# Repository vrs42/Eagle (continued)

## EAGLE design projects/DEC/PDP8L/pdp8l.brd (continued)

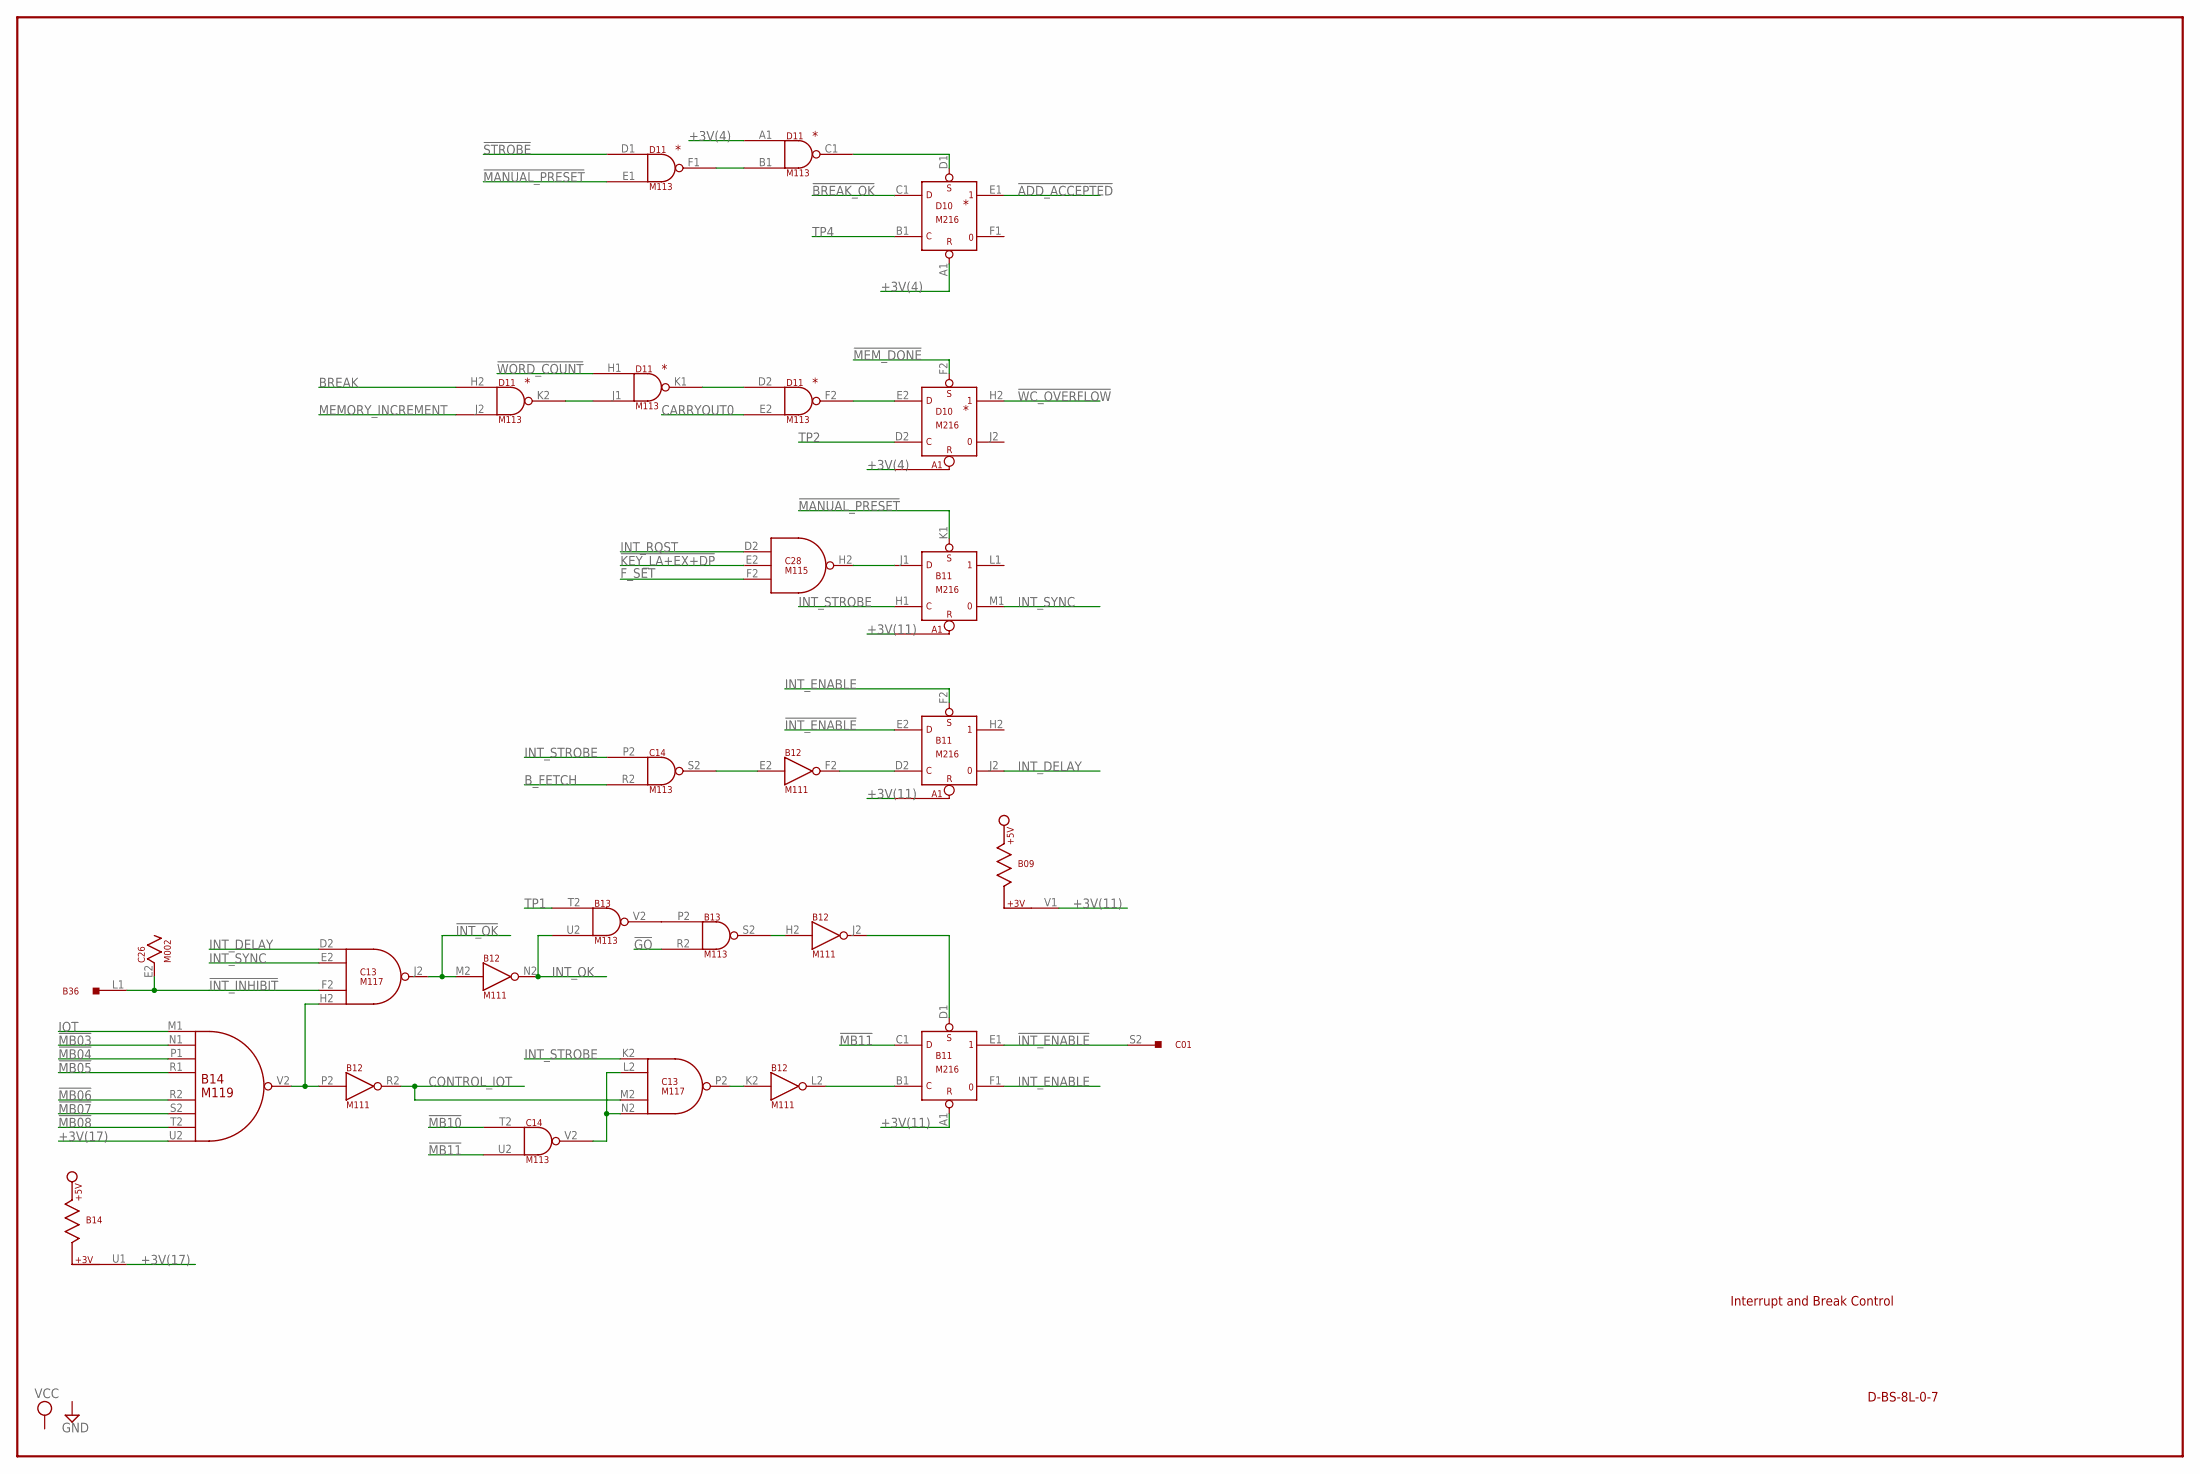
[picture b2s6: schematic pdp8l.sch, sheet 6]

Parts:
B09: M617; H807
B11: M216; H807
B12: M111; H807
B13: M113; H807
B14: M119; H807
B36: M903; H807
C01: G921; H807
C13: M117; H807
C14: M113; H807
C26: M002; H807
C28: M115; H807
D10: M216; H807
D11: M113; H807

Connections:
!ADD_ACCEPTED: D10.E1 (1); also elsewhere on the board
!BREAK_OK: D10.C1 (D); also elsewhere on the board
!GO: B13.R2 (IN2); also elsewhere on the board
!INT_ENABLE: B11.E1 (1), B11.E2 (D), C01.S2
!INT_INHIBIT: B36.L1, C13.F2 (IN3), C26.E2
!INT_OK: B12.M2 (IN), C13.J2 (OUT); also elsewhere on the board
!KEY_LA+EX+DP: C28.E2 (IN2); also elsewhere on the board
!MANUAL_PRESET: B11.K1 (S), D11.E1 (IN2); also elsewhere on the board
!MB03: B14.N1 (IN2); also elsewhere on the board
!MB04: B14.P1 (IN3); also elsewhere on the board
!MB05: B14.R1 (IN4); also elsewhere on the board
!MB06: B14.R2 (IN5); also elsewhere on the board
!MB07: B14.S2 (IN6); also elsewhere on the board
!MB08: B14.T2 (IN7); also elsewhere on the board
!MB10: C14.T2 (IN1); also elsewhere on the board
!MB11: B11.C1 (D), C14.U2 (IN2); also elsewhere on the board
!MEM_DONE: D10.F2 (S); also elsewhere on the board
!STROBE: D11.D1 (IN1); also elsewhere on the board
!WC_OVERFLOW: D10.H2 (1); also elsewhere on the board
!WORD_COUNT: D11.H1 (IN1); also elsewhere on the board
+3V(4): D10.A1 (R), D11.A1 (IN1); also elsewhere on the board
+3V(11): B09.V1, B11.A1 (R); also elsewhere on the board
+3V(17): B14.U1, B14.U2 (IN8)
B12F2: B11.D2 (C), B12.F2 (OUT)
B12J2: B11.D1 (S), B12.J2 (OUT)
B12L2: B11.B1 (C), B12.L2 (OUT)
B13S2: B12.H2 (IN), B13.S2 (OUT)
B13V2: B13.P2 (IN1), B13.V2 (OUT)
B14V2: B12.P2 (IN), B14.V2 (OUT), C13.H2 (IN4)
BREAK: D11.H2 (IN1); also elsewhere on the board
B_FETCH: C14.R2 (IN2); also elsewhere on the board
C13P2: B12.K2 (IN), C13.P2 (OUT)
C14S2: B12.E2 (IN), C14.S2 (OUT)
C14V2: C13.L2 (IN2), C13.N2 (IN4), C14.V2 (OUT)
C28H2: B11.J1 (D), C28.H2 (OUT)
CARRYOUT0: D11.E2 (IN2); also elsewhere on the board
CONTROL_IOT: B12.R2 (OUT), C13.M2 (IN3)
D11C1: D10.D1 (S), D11.C1 (OUT)
D11F1: D11.B1 (IN2), D11.F1 (OUT)
D11F2: D10.E2 (D), D11.F2 (OUT)
D11K1: D11.D2 (IN1), D11.K1 (OUT)
D11K2: D11.J1 (IN2), D11.K2 (OUT)
F_SET: C28.F2 (IN3); also elsewhere on the board
GND: B09.C2 (GND), B09.T1 (GND), B11.C2 (GND), B11.T1 (GND), B12.C2 (GND), B12.T1 (GND), B13.C2 (GND), B13.T1 (GND), B14.C2 (GND), B14.T1 (GND), B36.A1 (GND), B36.C1 (GND), B36.C2 (GND), B36.F1 (GND), B36.F2 (GND), B36.J2 (GND), B36.K1 (GND), B36.L2 (GND), B36.N1 (GND), B36.N2 (GND), B36.R1 (GND), B36.R2 (GND), B36.T1 (GND), B36.U2 (GND), C13.C2 (GND), C13.T1 (GND), C14.C2 (GND), C14.T1 (GND), C26.C2 (GND), C28.C2 (GND), C28.T1 (GND), D10.C2 (GND), D10.T1 (GND), D11.C2 (GND), D11.T1 (GND); also elsewhere on the board
INT_DELAY: B11.J2 (0), C13.D2 (IN1)
INT_ENABLE: B11.F1 (0), B11.F2 (S)
INT_OK: B12.N2 (OUT), B13.U2 (IN2); also elsewhere on the board
INT_RQST: C28.D2 (IN1); also elsewhere on the board
INT_STROBE: B11.H1 (C), C13.K2 (IN1), C14.P2 (IN1); also elsewhere on the board
INT_SYNC: B11.M1 (0), C13.E2 (IN2)
IOT: B14.M1 (IN1); also elsewhere on the board
MEMORY_INCREMENT: D11.J2 (IN2); also elsewhere on the board
TP1: B13.T2 (IN1); also elsewhere on the board
TP2: D10.D2 (C); also elsewhere on the board
TP4: D10.B1 (C); also elsewhere on the board
VCC: B09.A2 (VCC), B11.A2 (VCC), B12.A2 (VCC), B13.A2 (VCC), B14.A2 (VCC), C13.A2 (VCC), C14.A2 (VCC), C26.A2 (VCC), C28.A2 (VCC), D10.A2 (VCC), D11.A2 (VCC); also elsewhere on the board

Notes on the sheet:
D-BS-8L-0-7
Interrupt and Break Control

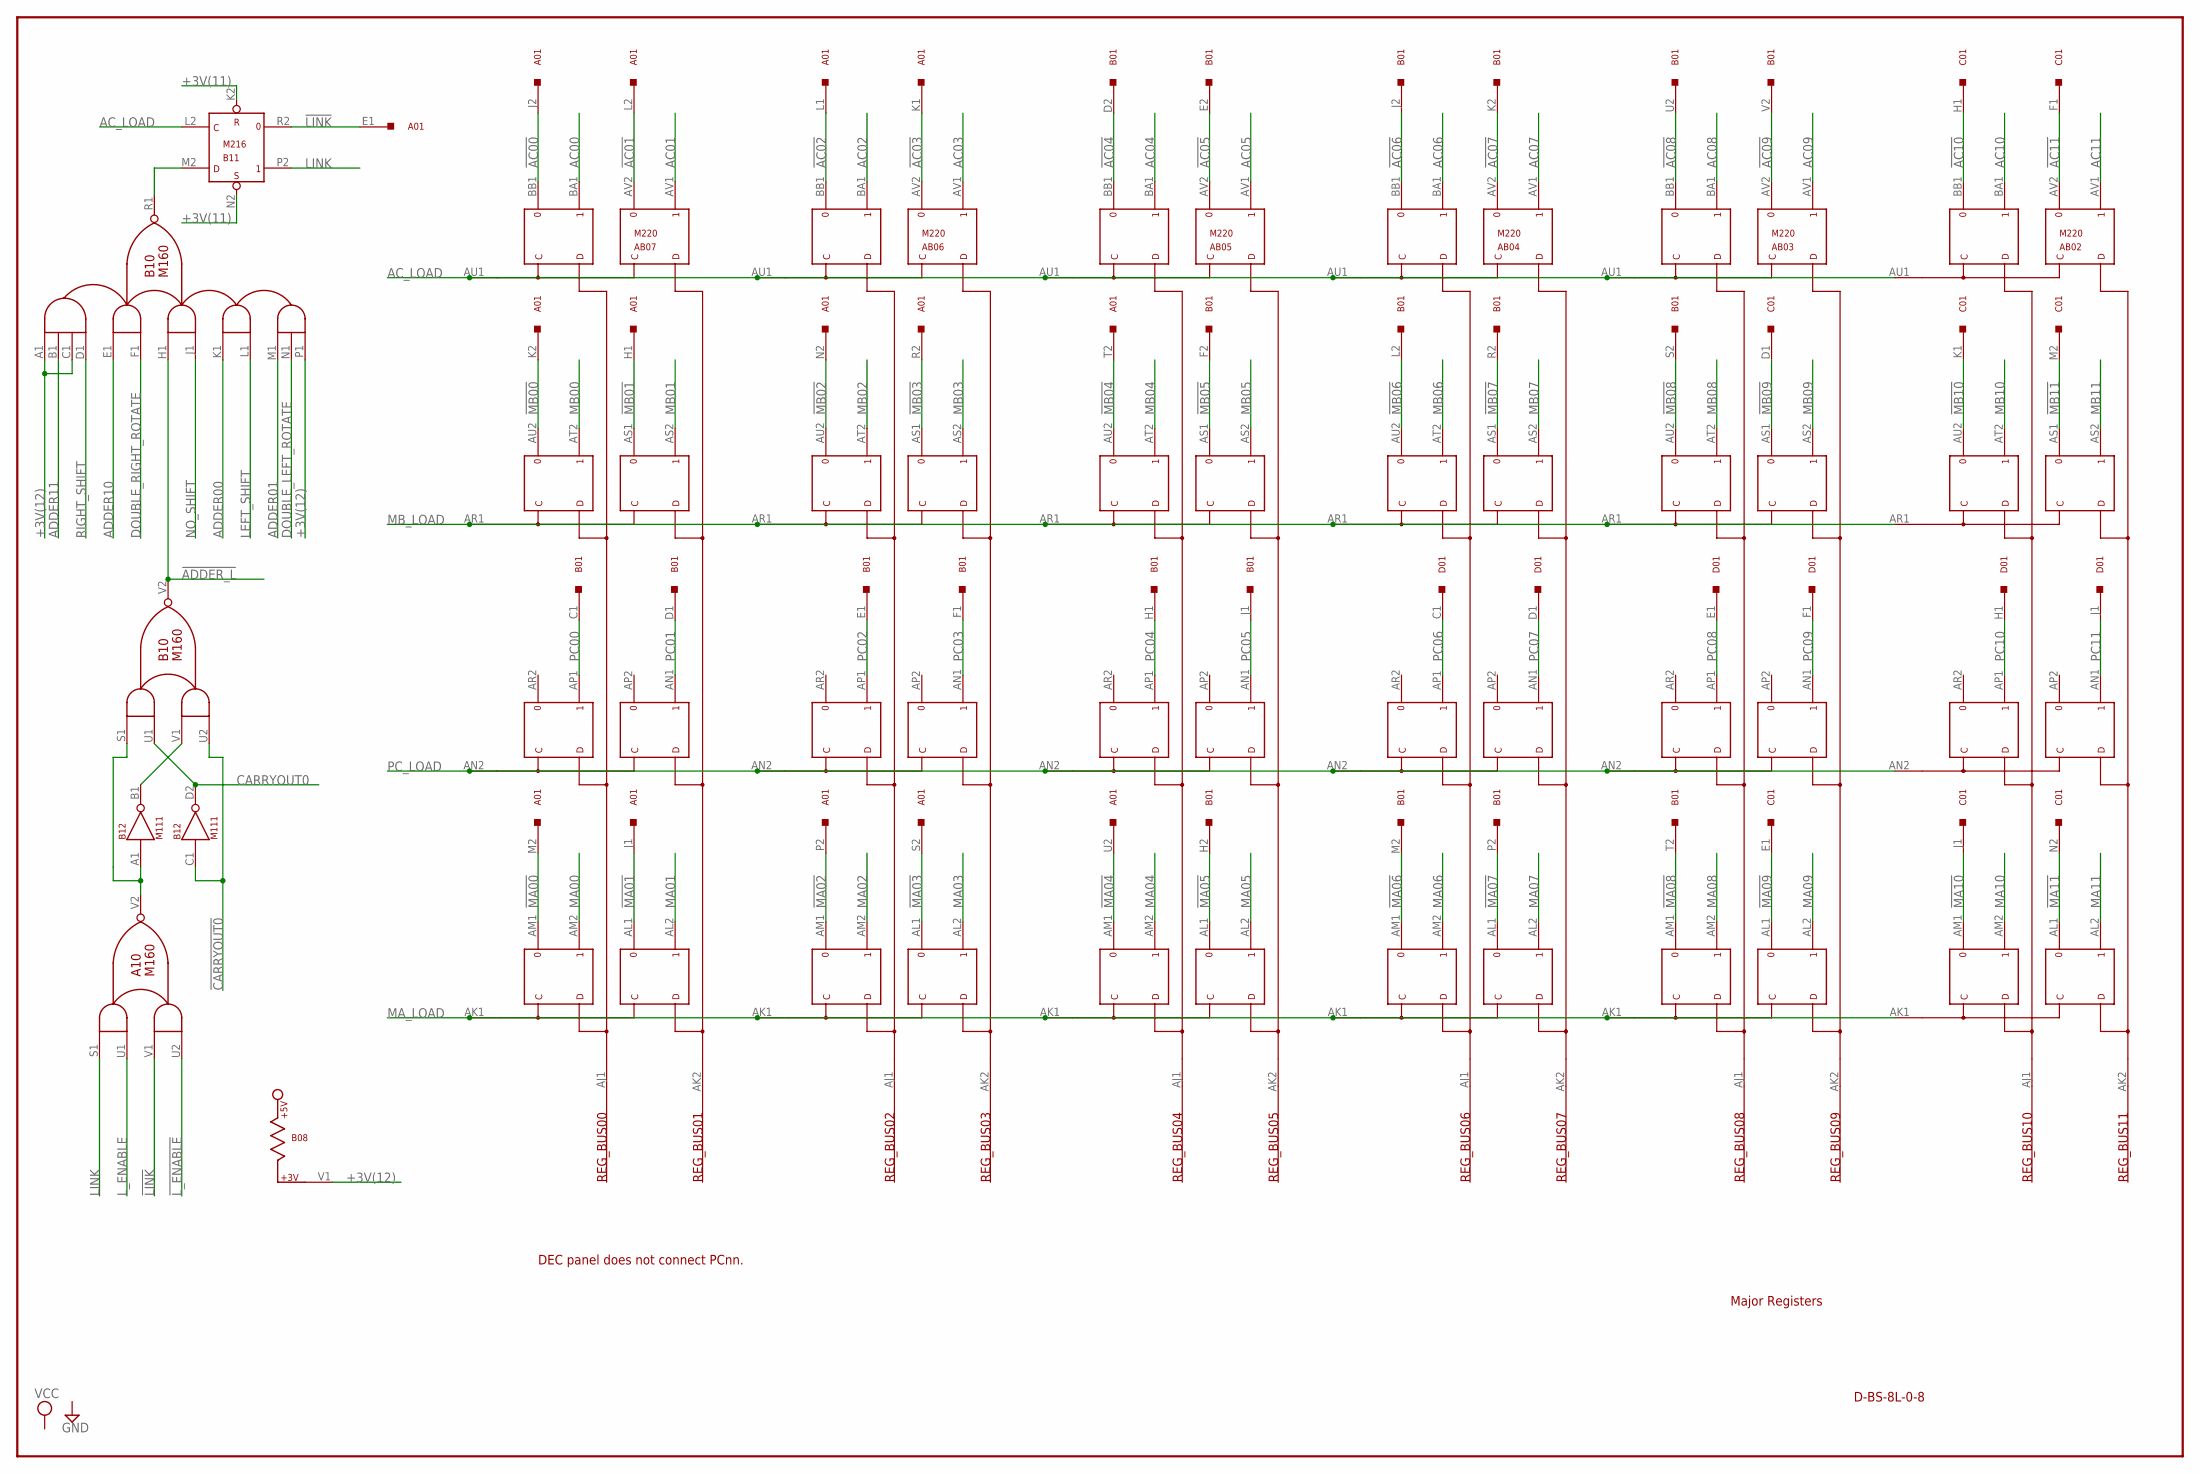
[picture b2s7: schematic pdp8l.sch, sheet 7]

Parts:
A01: G921; H807
A10: M160; H807
AB02, AB03, AB04, AB05, AB06, AB07: M220; H807-2
B01: G921; H807
B08: M617; H807
B10: M160; H807
B11: M216; H807
B12: M111; H807
C01: G921; H807
D01: G921; H807

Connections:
!AC00: A01.J2, AB07.BB1; also elsewhere on the board
!AC01: A01.L2, AB07.AV2; also elsewhere on the board
!AC02: A01.L1, AB06.BB1; also elsewhere on the board
!AC03: A01.K1, AB06.AV2; also elsewhere on the board
!AC04: AB05.BB1, B01.D2; also elsewhere on the board
!AC05: AB05.AV2, B01.E2; also elsewhere on the board
!AC06: AB04.BB1, B01.J2; also elsewhere on the board
!AC07: AB04.AV2, B01.K2; also elsewhere on the board
!AC08: AB03.BB1, B01.U2; also elsewhere on the board
!AC09: AB03.AV2, B01.V2; also elsewhere on the board
!AC10: AB02.BB1, C01.H1; also elsewhere on the board
!AC11: AB02.AV2, C01.F1; also elsewhere on the board
!ADDER_L: B10.H1 (IN3A), B10.V2 (OUT); also elsewhere on the board
!CARRYOUT0: B10.U2 (IN2B), B12.C1 (IN); also elsewhere on the board
!LINK: A01.E1, A10.V1 (IN2A), B11.R2 (0)
!L_ENABLE: A10.U2 (IN2B); also elsewhere on the board
!MA00: A01.M2, AB07.AM1; also elsewhere on the board
!MA01: A01.J1, AB07.AL1; also elsewhere on the board
!MA02: A01.P2, AB06.AM1; also elsewhere on the board
!MA03: A01.S2, AB06.AL1; also elsewhere on the board
!MA04: A01.U2, AB05.AM1; also elsewhere on the board
!MA05: AB05.AL1, B01.H2; also elsewhere on the board
!MA06: AB04.AM1, B01.M2; also elsewhere on the board
!MA07: AB04.AL1, B01.P2; also elsewhere on the board
!MA08: AB03.AM1, B01.T2; also elsewhere on the board
!MA09: AB03.AL1, C01.E1; also elsewhere on the board
!MA10: AB02.AM1, C01.J1; also elsewhere on the board
!MA11: AB02.AL1, C01.N2; also elsewhere on the board
!MB00: A01.K2, AB07.AU2; also elsewhere on the board
!MB01: A01.H1, AB07.AS1; also elsewhere on the board
!MB02: A01.N2, AB06.AU2; also elsewhere on the board
!MB03: A01.R2, AB06.AS1; also elsewhere on the board
!MB04: A01.T2, AB05.AU2; also elsewhere on the board
!MB05: AB05.AS1, B01.F2; also elsewhere on the board
!MB06: AB04.AU2, B01.L2; also elsewhere on the board
!MB07: AB04.AS1, B01.R2; also elsewhere on the board
!MB08: AB03.AU2, B01.S2; also elsewhere on the board
!MB09: AB03.AS1, C01.D1; also elsewhere on the board
!MB10: AB02.AU2, C01.K1; also elsewhere on the board
!MB11: AB02.AS1, C01.M2; also elsewhere on the board
+3V(11): B11.K2 (R), B11.N2 (S); also elsewhere on the board
+3V(12): B08.V1, B10.A1 (IN1A), B10.C1 (IN1C), B10.P1 (IN5C)
A10V2: A10.V2 (OUT), B10.S1 (IN1A), B12.A1 (IN)
AC00: AB07.BA1; also elsewhere on the board
AC01: AB07.AV1; also elsewhere on the board
AC02: AB06.BA1; also elsewhere on the board
AC03: AB06.AV1; also elsewhere on the board
AC04: AB05.BA1; also elsewhere on the board
AC05: AB05.AV1; also elsewhere on the board
AC06: AB04.BA1; also elsewhere on the board
AC07: AB04.AV1; also elsewhere on the board
AC08: AB03.BA1; also elsewhere on the board
AC09: AB03.AV1; also elsewhere on the board
AC10: AB02.BA1; also elsewhere on the board
AC11: AB02.AV1; also elsewhere on the board
AC_LOAD: AB02.AU1, AB03.AU1, AB04.AU1, AB05.AU1, AB06.AU1, AB07.AU1, B11.L2 (C); also elsewhere on the board
ADDER00: B10.K1 (IN4A); also elsewhere on the board
ADDER01: B10.M1 (IN5A); also elsewhere on the board
ADDER10: B10.E1 (IN2A); also elsewhere on the board
ADDER11: B10.B1 (IN1B); also elsewhere on the board
B10R1: B10.R1 (OUT), B11.M2 (D)
B12B1: B10.V1 (IN2A), B12.B1 (OUT)
CARRYOUT0: B10.U1 (IN1B), B12.D2 (OUT); also elsewhere on the board
DOUBLE_LEFT_ROTATE: B10.N1 (IN5B); also elsewhere on the board
DOUBLE_RIGHT_ROTATE: B10.F1 (IN2B); also elsewhere on the board
GND: A10.C2 (GND), A10.T1 (GND), AB02.AC2 (GND), AB02.AT1 (GND), AB02.BC2 (GND), AB02.BT1 (GND), AB03.AC2 (GND), AB03.AT1 (GND), AB03.BC2 (GND), AB03.BT1 (GND), AB04.AC2 (GND), AB04.AT1 (GND), AB04.BC2 (GND), AB04.BT1 (GND), AB05.AC2 (GND), AB05.AT1 (GND), AB05.BC2 (GND), AB05.BT1 (GND), AB06.AC2 (GND), AB06.AT1 (GND), AB06.BC2 (GND), AB06.BT1 (GND), AB07.AC2 (GND), AB07.AT1 (GND), AB07.BC2 (GND), AB07.BT1 (GND), B08.C2 (GND), B08.T1 (GND), B10.C2 (GND), B10.T1 (GND), B11.C2 (GND), B11.T1 (GND), B12.C2 (GND), B12.T1 (GND); also elsewhere on the board
LEFT_SHIFT: B10.L1 (IN4B); also elsewhere on the board
LINK: A10.S1 (IN1A), B11.P2 (1); also elsewhere on the board
L_ENABLE: A10.U1 (IN1B); also elsewhere on the board
MA00: AB07.AM2; also elsewhere on the board
MA01: AB07.AL2; also elsewhere on the board
MA02: AB06.AM2; also elsewhere on the board
MA03: AB06.AL2; also elsewhere on the board
MA04: AB05.AM2; also elsewhere on the board
MA05: AB05.AL2; also elsewhere on the board
MA06: AB04.AM2; also elsewhere on the board
MA07: AB04.AL2; also elsewhere on the board
MA08: AB03.AM2; also elsewhere on the board
MA09: AB03.AL2; also elsewhere on the board
MA10: AB02.AM2; also elsewhere on the board
MA11: AB02.AL2; also elsewhere on the board
MA_LOAD: AB02.AK1, AB03.AK1, AB04.AK1, AB05.AK1, AB06.AK1, AB07.AK1; also elsewhere on the board
MB00: AB07.AT2; also elsewhere on the board
MB01: AB07.AS2; also elsewhere on the board
MB02: AB06.AT2; also elsewhere on the board
MB03: AB06.AS2; also elsewhere on the board
MB04: AB05.AT2; also elsewhere on the board
MB05: AB05.AS2; also elsewhere on the board
MB06: AB04.AT2; also elsewhere on the board
MB07: AB04.AS2; also elsewhere on the board
MB08: AB03.AT2; also elsewhere on the board
MB09: AB03.AS2; also elsewhere on the board
MB10: AB02.AT2; also elsewhere on the board
MB11: AB02.AS2; also elsewhere on the board
MB_LOAD: AB02.AR1, AB03.AR1, AB04.AR1, AB05.AR1, AB06.AR1, AB07.AR1; also elsewhere on the board
NO_SHIFT: B10.J1 (IN3B); also elsewhere on the board
PC00: AB07.AP1, B01.C1
PC01: AB07.AN1, B01.D1
PC02: AB06.AP1, B01.E1
PC03: AB06.AN1, B01.F1
PC04: AB05.AP1, B01.H1
PC05: AB05.AN1, B01.J1
PC06: AB04.AP1, D01.C1
PC07: AB04.AN1, D01.D1
PC08: AB03.AP1, D01.E1
PC09: AB03.AN1, D01.F1
PC10: AB02.AP1, D01.H1
PC11: AB02.AN1, D01.J1
PC_LOAD: AB02.AN2, AB03.AN2, AB04.AN2, AB05.AN2, AB06.AN2, AB07.AN2; also elsewhere on the board
RIGHT_SHIFT: B10.D1 (IN1D); also elsewhere on the board
VCC: A10.A2 (VCC), AB02.AA2 (VCC), AB02.BA2 (VCC), AB03.AA2 (VCC), AB03.BA2 (VCC), AB04.AA2 (VCC), AB04.BA2 (VCC), AB05.AA2 (VCC), AB05.BA2 (VCC), AB06.AA2 (VCC), AB06.BA2 (VCC), AB07.AA2 (VCC), AB07.BA2 (VCC), B08.A2 (VCC), B10.A2 (VCC), B11.A2 (VCC), B12.A2 (VCC); also elsewhere on the board

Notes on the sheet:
Major Registers
D-BS-8L-0-8
REG_BUS00
REG_BUS01
REG_BUS02
REG_BUS03
REG_BUS04
REG_BUS05
REG_BUS06
REG_BUS07
REG_BUS08
REG_BUS09
REG_BUS10
REG_BUS11
DEC panel does not connect PCnn.

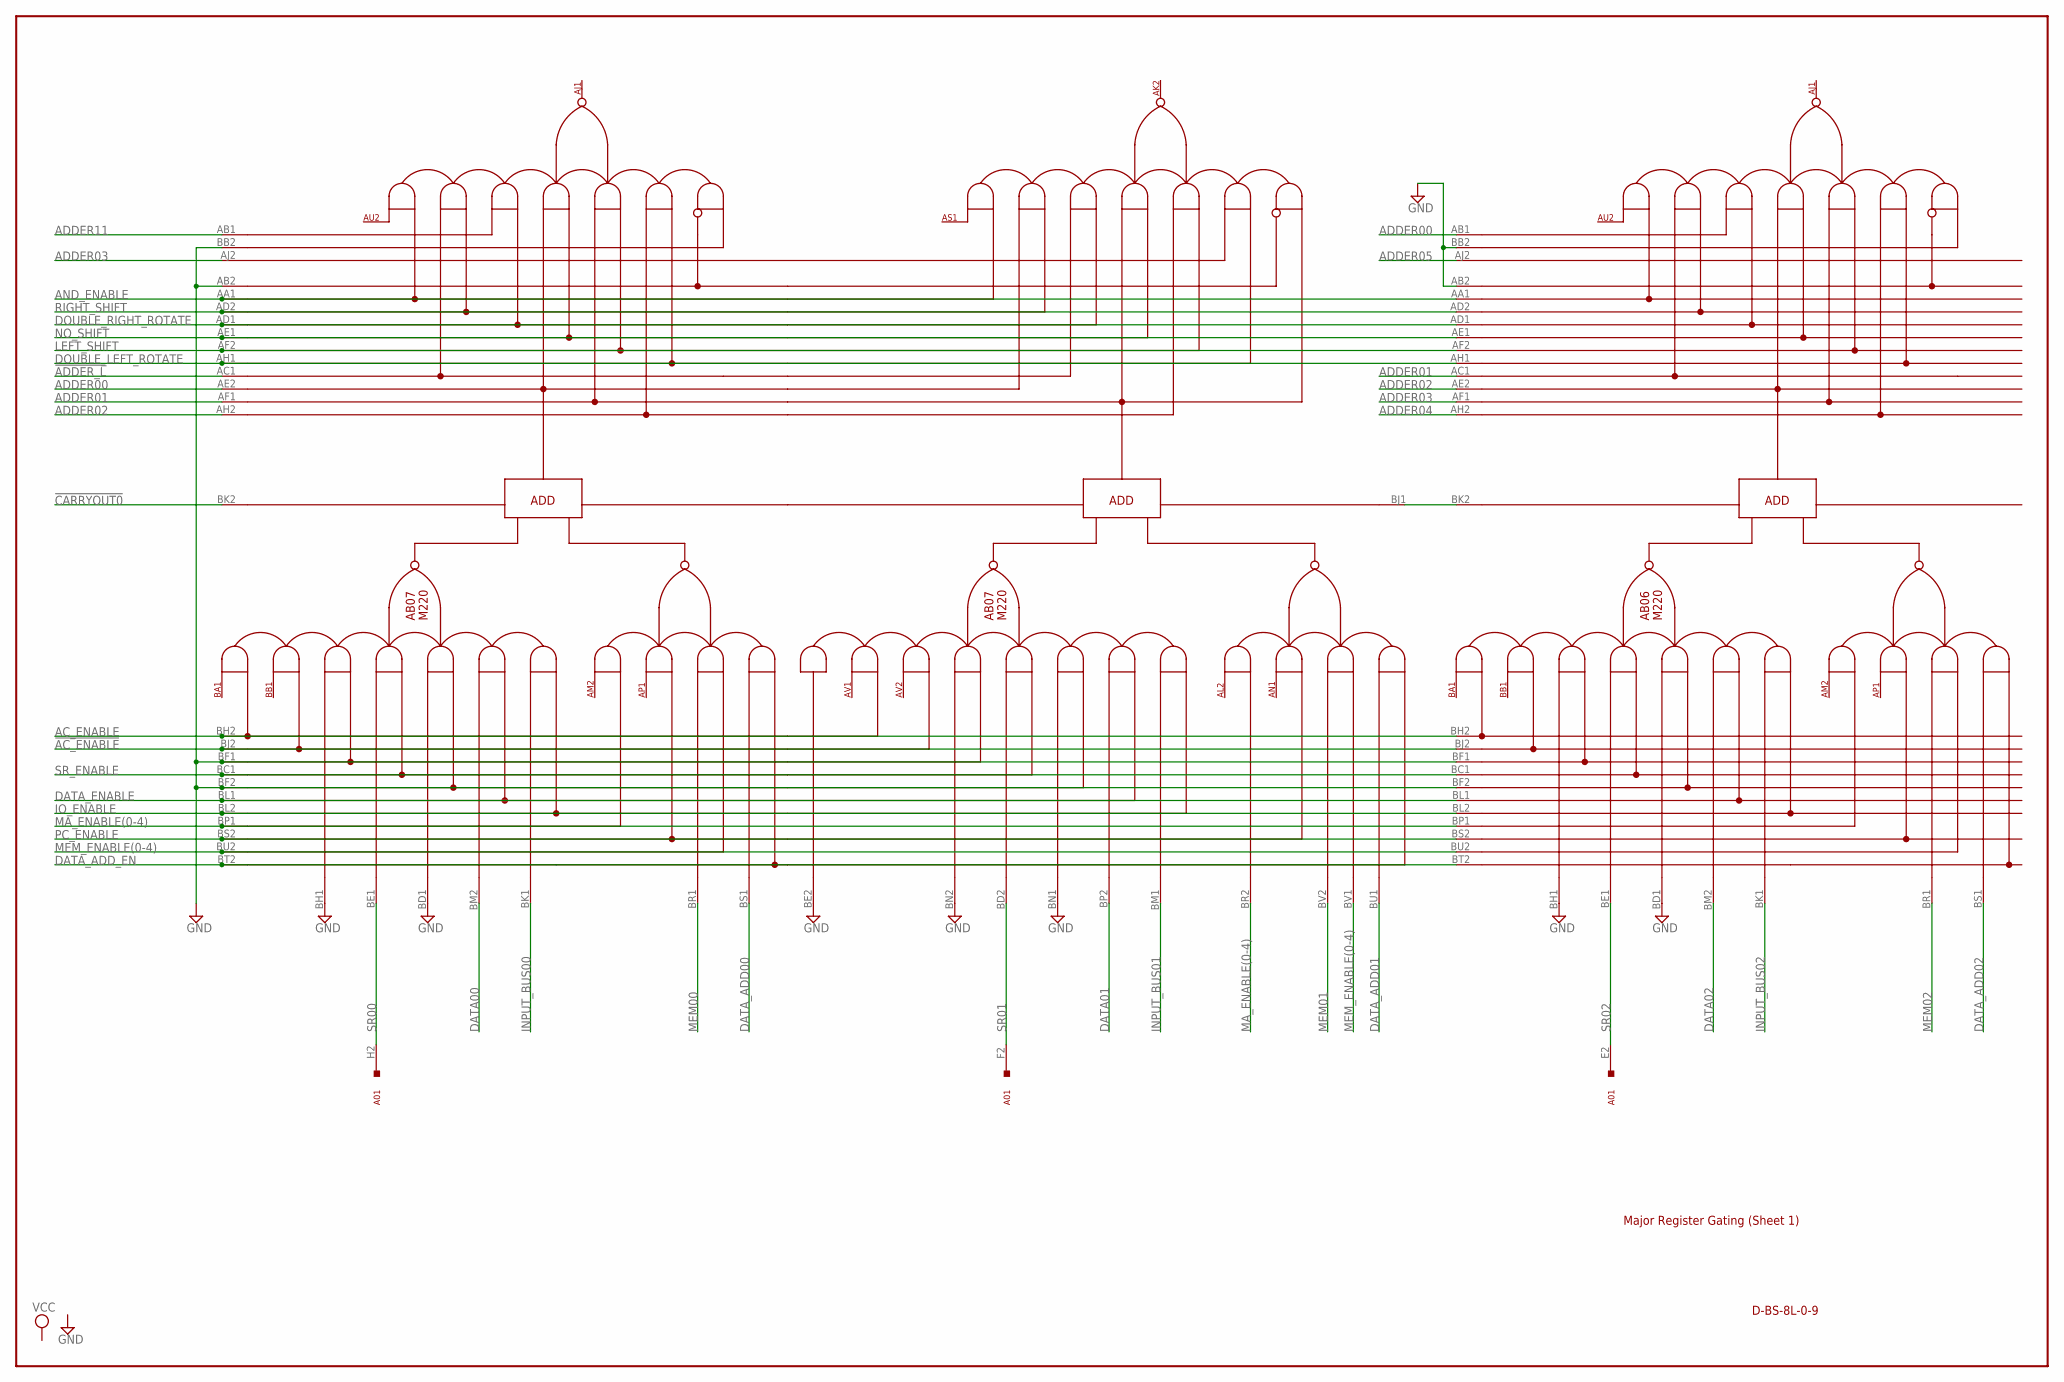
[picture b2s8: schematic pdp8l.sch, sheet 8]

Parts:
A01: G921; H807
AB06, AB07: M220; H807-2

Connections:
!AC_ENABLE: AB06.BJ2, AB07.BJ2; also elsewhere on the board
!ADDER_L: AB07.AC1; also elsewhere on the board
!CARRYOUT0: AB07.BK2; also elsewhere on the board
!CARRYOUT2: AB06.BK2, AB07.BJ1
AC_ENABLE: AB06.BH2, AB07.BH2; also elsewhere on the board
ADDER00: AB06.AB1, AB07.AE2; also elsewhere on the board
ADDER01: AB06.AC1, AB07.AF1; also elsewhere on the board
ADDER02: AB06.AE2, AB07.AH2; also elsewhere on the board
ADDER03: AB06.AF1, AB07.AJ2; also elsewhere on the board
ADDER04: AB06.AH2; also elsewhere on the board
ADDER05: AB06.AJ2; also elsewhere on the board
ADDER11: AB07.AB1; also elsewhere on the board
AND_ENABLE: AB06.AA1, AB07.AA1; also elsewhere on the board
DATA00: AB07.BM2; also elsewhere on the board
DATA01: AB07.BP2; also elsewhere on the board
DATA02: AB06.BM2; also elsewhere on the board
DATA_ADD00: AB07.BS1; also elsewhere on the board
DATA_ADD01: AB07.BU1; also elsewhere on the board
DATA_ADD02: AB06.BS1; also elsewhere on the board
DATA_ADD_EN: AB06.BT2, AB07.BT2; also elsewhere on the board
DATA_ENABLE: AB06.BL1, AB07.BL1; also elsewhere on the board
DOUBLE_LEFT_ROTATE: AB06.AH1, AB07.AH1; also elsewhere on the board
DOUBLE_RIGHT_ROTATE: AB06.AD1, AB07.AD1; also elsewhere on the board
GND: AB06.AB2, AB06.AC2 (GND), AB06.AT1 (GND), AB06.BB2, AB06.BC2 (GND), AB06.BD1, AB06.BF1, AB06.BF2, AB06.BH1, AB06.BT1 (GND), AB07.AB2, AB07.AC2 (GND), AB07.AT1 (GND), AB07.BB2, AB07.BC2 (GND), AB07.BD1, AB07.BE2, AB07.BF1, AB07.BF2, AB07.BH1, AB07.BN1, AB07.BN2, AB07.BT1 (GND); also elsewhere on the board
INPUT_BUS00: AB07.BK1; also elsewhere on the board
INPUT_BUS01: AB07.BM1; also elsewhere on the board
INPUT_BUS02: AB06.BK1; also elsewhere on the board
IO_ENABLE: AB06.BL2, AB07.BL2; also elsewhere on the board
LEFT_SHIFT: AB06.AF2, AB07.AF2; also elsewhere on the board
MA_ENABLE(0-4): AB06.BP1, AB07.BP1, AB07.BR2; also elsewhere on the board
MEM00: AB07.BR1; also elsewhere on the board
MEM01: AB07.BV2; also elsewhere on the board
MEM02: AB06.BR1; also elsewhere on the board
MEM_ENABLE(0-4): AB06.BU2, AB07.BU2, AB07.BV1; also elsewhere on the board
NO_SHIFT: AB06.AE1, AB07.AE1; also elsewhere on the board
PC_ENABLE: AB06.BS2, AB07.BS2; also elsewhere on the board
RIGHT_SHIFT: AB06.AD2, AB07.AD2; also elsewhere on the board
SR00: A01.H2, AB07.BE1
SR01: A01.F2, AB07.BD2
SR02: A01.E2, AB06.BE1
SR_ENABLE: AB06.BC1, AB07.BC1; also elsewhere on the board
VCC: AB06.AA2 (VCC), AB06.BA2 (VCC), AB07.AA2 (VCC), AB07.BA2 (VCC); also elsewhere on the board

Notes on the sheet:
Major Register Gating (Sheet 1)
D-BS-8L-0-9

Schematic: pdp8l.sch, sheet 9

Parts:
A01: G921; H807
AB05, AB06: M220; H807-2
C01: G921; H807

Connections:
!AC_ENABLE: AB05.BJ2; also elsewhere on the board
!CARRYOUT4: AB05.BK2, AB06.BJ1
!CARRYOUT6: AB05.BJ1; also elsewhere on the board
AC_ENABLE: AB05.BH2; also elsewhere on the board
ADDER02: AB05.AB1; also elsewhere on the board
ADDER03: AB05.AC1; also elsewhere on the board
ADDER04: AB05.AE2; also elsewhere on the board
ADDER05: AB05.AF1; also elsewhere on the board
ADDER06: AB05.AH2; also elsewhere on the board
ADDER07: AB05.AJ2; also elsewhere on the board
AND_ENABLE: AB05.AA1; also elsewhere on the board
DATA03: AB06.BP2; also elsewhere on the board
DATA04: AB05.BM2; also elsewhere on the board
DATA05: AB05.BP2; also elsewhere on the board
DATA_ADD03: AB06.BU1; also elsewhere on the board
DATA_ADD04: AB05.BS1; also elsewhere on the board
DATA_ADD05: AB05.BU1; also elsewhere on the board
DATA_ADD_EN: AB05.BT2; also elsewhere on the board
DATA_ENABLE: AB05.BL1; also elsewhere on the board
DOUBLE_LEFT_ROTATE: AB05.AH1; also elsewhere on the board
DOUBLE_RIGHT_ROTATE: AB05.AD1; also elsewhere on the board
GND: AB05.AB2, AB05.AC2 (GND), AB05.AT1 (GND), AB05.BB2, AB05.BC2 (GND), AB05.BD1, AB05.BE2, AB05.BF1, AB05.BF2, AB05.BH1, AB05.BN1, AB05.BN2, AB05.BT1 (GND), AB06.AC2 (GND), AB06.AT1 (GND), AB06.BC2 (GND), AB06.BE2, AB06.BN1, AB06.BN2, AB06.BT1 (GND); also elsewhere on the board
INPUT_BUS03: AB06.BM1; also elsewhere on the board
INPUT_BUS04: AB05.BK1; also elsewhere on the board
INPUT_BUS05: AB05.BM1; also elsewhere on the board
IO_ENABLE: AB05.BL2; also elsewhere on the board
LEFT_SHIFT: AB05.AF2; also elsewhere on the board
MA_ENABLE(0-4): AB05.BP1, AB06.BR2; also elsewhere on the board
MA_ENABLE(5-11): AB05.BR2; also elsewhere on the board
MEM03: AB06.BV2; also elsewhere on the board
MEM04: AB05.BR1; also elsewhere on the board
MEM05: AB05.BV2; also elsewhere on the board
MEM_ENABLE(0-4): AB05.BU2, AB06.BV1; also elsewhere on the board
MEM_ENABLE(5-11): AB05.BV1; also elsewhere on the board
NO_SHIFT: AB05.AE1; also elsewhere on the board
PC_ENABLE: AB05.BS2; also elsewhere on the board
RIGHT_SHIFT: AB05.AD2; also elsewhere on the board
SR03: A01.D2, AB06.BD2
SR04: A01.D1, AB05.BE1
SR05: AB05.BD2, C01.L2
SR_ENABLE: AB05.BC1; also elsewhere on the board
VCC: AB05.AA2 (VCC), AB05.BA2 (VCC), AB06.AA2 (VCC), AB06.BA2 (VCC); also elsewhere on the board

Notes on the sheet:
D-BS-8L-0-9
Major Register Gating (Sheet 2)

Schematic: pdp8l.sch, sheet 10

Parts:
AB03, AB04: M220; H807-2
C01: G921; H807

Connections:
!AC_ENABLE: AB03.BJ2, AB04.BJ2; also elsewhere on the board
!CARRYOUT6: AB04.BK2; also elsewhere on the board
!CARRYOUT8: AB03.BK2, AB04.BJ1
AC_ENABLE: AB03.BH2, AB04.BH2; also elsewhere on the board
ADDER04: AB04.AB1; also elsewhere on the board
ADDER05: AB04.AC1; also elsewhere on the board
ADDER06: AB03.AB1, AB04.AE2; also elsewhere on the board
ADDER07: AB03.AC1, AB04.AF1; also elsewhere on the board
ADDER08: AB03.AE2, AB04.AH2; also elsewhere on the board
ADDER09: AB03.AF1, AB04.AJ2; also elsewhere on the board
ADDER10: AB03.AH2; also elsewhere on the board
ADDER11: AB03.AJ2; also elsewhere on the board
AND_ENABLE: AB03.AA1, AB04.AA1; also elsewhere on the board
DATA06: AB04.BM2; also elsewhere on the board
DATA07: AB04.BP2; also elsewhere on the board
DATA08: AB03.BM2; also elsewhere on the board
DATA_ADD06: AB04.BS1; also elsewhere on the board
DATA_ADD07: AB04.BU1; also elsewhere on the board
DATA_ADD08: AB03.BS1; also elsewhere on the board
DATA_ADD_EN: AB03.BT2, AB04.BT2; also elsewhere on the board
DATA_ENABLE: AB03.BL1, AB04.BL1; also elsewhere on the board
DOUBLE_LEFT_ROTATE: AB03.AH1, AB04.AH1; also elsewhere on the board
DOUBLE_RIGHT_ROTATE: AB03.AD1, AB04.AD1; also elsewhere on the board
GND: AB03.AB2, AB03.AC2 (GND), AB03.AT1 (GND), AB03.BB2, AB03.BC2 (GND), AB03.BD1, AB03.BF1, AB03.BF2, AB03.BH1, AB03.BT1 (GND), AB04.AB2, AB04.AC2 (GND), AB04.AT1 (GND), AB04.BB2, AB04.BC2 (GND), AB04.BD1, AB04.BE2, AB04.BF1, AB04.BF2, AB04.BH1, AB04.BN1, AB04.BN2, AB04.BT1 (GND); also elsewhere on the board
INPUT_BUS06: AB04.BK1; also elsewhere on the board
INPUT_BUS07: AB04.BM1; also elsewhere on the board
INPUT_BUS08: AB03.BK1; also elsewhere on the board
IO_ENABLE: AB03.BL2, AB04.BL2; also elsewhere on the board
LEFT_SHIFT: AB03.AF2, AB04.AF2; also elsewhere on the board
MA_ENABLE(5-11): AB03.BP1, AB04.BP1, AB04.BR2; also elsewhere on the board
MEM06: AB04.BR1; also elsewhere on the board
MEM07: AB04.BV2; also elsewhere on the board
MEM08: AB03.BR1; also elsewhere on the board
MEM_ENABLE(5-11): AB03.BU2, AB04.BU2, AB04.BV1; also elsewhere on the board
NO_SHIFT: AB03.AE1, AB04.AE1; also elsewhere on the board
PC_ENABLE: AB03.BS2, AB04.BS2; also elsewhere on the board
RIGHT_SHIFT: AB03.AD2, AB04.AD2; also elsewhere on the board
SR06: AB04.BE1, C01.K2
SR07: AB04.BD2, C01.J2
SR08: AB03.BE1, C01.H2
SR_ENABLE: AB03.BC1, AB04.BC1; also elsewhere on the board
VCC: AB03.AA2 (VCC), AB03.BA2 (VCC), AB04.AA2 (VCC), AB04.BA2 (VCC); also elsewhere on the board

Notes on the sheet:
Major Register Gating (Sheet 3)
D-BS-8L-0-9

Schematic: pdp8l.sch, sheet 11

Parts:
AB02, AB03: M220; H807-2
C01: G921; H807
D01: G921; H807

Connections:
!AC_ENABLE: AB02.BJ2; also elsewhere on the board
!ADDER_L: AB02.AH2; also elsewhere on the board
!CARRYOUT10: AB02.BK2, AB03.BJ1
AC_ENABLE: AB02.BH2; also elsewhere on the board
ADDER00: AB02.AJ2; also elsewhere on the board
ADDER08: AB02.AB1; also elsewhere on the board
ADDER09: AB02.AC1; also elsewhere on the board
ADDER10: AB02.AE2; also elsewhere on the board
ADDER11: AB02.AF1; also elsewhere on the board
AND_ENABLE: AB02.AA1; also elsewhere on the board
CARRY_INSERT: AB02.BJ1; also elsewhere on the board
DATA09: AB03.BP2; also elsewhere on the board
DATA10: AB02.BM2; also elsewhere on the board
DATA11: AB02.BP2; also elsewhere on the board
DATA_ADD09: AB03.BU1; also elsewhere on the board
DATA_ADD10: AB02.BS1; also elsewhere on the board
DATA_ADD11: AB02.BU1; also elsewhere on the board
DATA_ADD_EN: AB02.BT2; also elsewhere on the board
DATA_ENABLE: AB02.BL1; also elsewhere on the board
DOUBLE_LEFT_ROTATE: AB02.AH1; also elsewhere on the board
DOUBLE_RIGHT_ROTATE: AB02.AD1; also elsewhere on the board
GND: AB02.AB2, AB02.AC2 (GND), AB02.AT1 (GND), AB02.BB2, AB02.BC2 (GND), AB02.BD1, AB02.BE2, AB02.BF1, AB02.BF2, AB02.BH1, AB02.BN1, AB02.BN2, AB02.BT1 (GND), AB03.AC2 (GND), AB03.AT1 (GND), AB03.BC2 (GND), AB03.BE2, AB03.BN1, AB03.BN2, AB03.BT1 (GND); also elsewhere on the board
INPUT_BUS09: AB03.BM1; also elsewhere on the board
INPUT_BUS10: AB02.BK1; also elsewhere on the board
INPUT_BUS11: AB02.BM1; also elsewhere on the board
IO_ENABLE: AB02.BL2; also elsewhere on the board
LEFT_SHIFT: AB02.AF2; also elsewhere on the board
MA_ENABLE(5-11): AB02.BP1, AB02.BR2, AB03.BR2; also elsewhere on the board
MEM09: AB03.BV2; also elsewhere on the board
MEM10: AB02.BR1; also elsewhere on the board
MEM11: AB02.BV2; also elsewhere on the board
MEM_ENABLE(5-11): AB02.BU2, AB02.BV1, AB03.BV1; also elsewhere on the board
NO_SHIFT: AB02.AE1; also elsewhere on the board
PC_ENABLE: AB02.BS2; also elsewhere on the board
RIGHT_SHIFT: AB02.AD2; also elsewhere on the board
SR09: AB03.BD2, C01.E2
SR10: AB02.BE1, C01.F2
SR11: AB02.BD2, D01.M2
SR_ENABLE: AB02.BC1; also elsewhere on the board
VCC: AB02.AA2 (VCC), AB02.BA2 (VCC), AB03.AA2 (VCC), AB03.BA2 (VCC); also elsewhere on the board

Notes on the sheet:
D-BS-8L-0-9
Major Register Gating (Sheet 4)
